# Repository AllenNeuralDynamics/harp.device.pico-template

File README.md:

# harp.device.pico-template

An RP2040-based Harp hardware/firmware project template.

## Features
* predefined *.gitignore* file to remove extraneous KiCAD (hardware) files.
### Hardware
* Schematic template for a generic Harp Device including:
  * ground-isolated Full Speed USB communication
  * 3.5mm audio jack for Harp-protocol time synchronization
  * RP2040 MCU and required "jellybean" components including:
    * 2MB external flash (Winbond MPN: W25Q16JVUXIQ TR).
  * 2 power supply chain options for power derived from either USB directly or from a DC barrel jack.
* Basic PCBA Layout with size hints for various existing enclosures
  * DC Barrel Jack (2.1 x 5.5mm, positive center)
  * USBC
  * 3.5mm audio jack for Harp synchronization signal
  * Ground lug
### Firmware
* basic "hello-world" project with corresponding file structure
* populated CMakeLists.txt for compliation
* placeholder USB descriptors for Manufacturer and Description fields (in the CMakeLists.txt)
* compilation [instructions](./firmware/README.md)
* harp protocol core library included as a submodule [harp.core.rp2040](https://github.com/AllenNeuralDynamics/harp.core.rp2040)

# Using this template
Start by clicking the "Use this Template" button in the upper right corner, or click [here](https://github.com/new?template_name=harp.device.pico-template&template_owner=AllenNeuralDynamics).
## Repository Setup
* If the project has a corresponding Allen Institute SIPE project number, prepend the repository description with: `{SIPE Project Number}:`.
* add the tag `Harp`
* Long-term: remove these instructions!

## Hardware
* Remove all unused hardware folder starter projects.
* 🔧 Design your hardware.
* In the PCBA silkscreen, add:
  * SIPE part number with full hardware semantic version appended in the format: `{SIPE Project Number}-E-{hw major}-{hw minor}-{hw patch}`. Version number fields range from 1-999 and include leading zeros.
  * [QR code](https://www.the-qrcode-generator.com/) linking to the Github repository.

## Firmware
* Update the *Manufacturer* and *Description* USB descriptors in the CMakeLists.txt
* 📝 Write your firmware.

# Github Release Conventions
Releases specify any vetted changes to the hardware or firmware.

Each release specifies:
* semantic versions of changed elements: hardware or firmware.
* SIPE part number (or part numbers if multiple are compatible)

Each hardware release includes:
* STEP file of the PCB named with the SIPE part number
* schematic (PDF)
* Gerber files (with logos removed) of the PCBA
* Position files for component placement
* Bill-of-Materials for the PCBA

Each hardware release specifies:
* compatible SIPE part number(s)

> [!NOTE]
> SIPE part numbers only encode hardware semantic version major number, so multiple minor/patch hardware releases may point to the same SIPE part number.

> [!NOTE]
> It is possible for a project to have PCBA variants--possibly with very different functionality. In this case, reserve a hardware major version range (>100 suggested) for this variant and treat it as a distinct hardware release (i.e: with all corresponding included hardware files).

Each firmware release specifies:
* firmware semantic version
* compatible hardware (SIPE part number or part number range).

Each firmware release includes:
* compiled binary file (**\*.uf2**) of the firmware.

## Release Title
The release title is specified as follows:

`hw{hw major}.{hw minor}.{hw patch}-fw{fw major}.{fw minor}.{fw patch}`

If the release has firmware-only changes, you can drop the `hw*` section, and vice versa.

> [!NOTE]
> After Oct 2024, hardware major fields on all future releases will be equivalent to the major version number of the SIPE part number. See the [SIPE PCBA part numbering standard](https://alleninstitute.sharepoint.com/:w:/s/Instrumentation/EYsRN8q4jHJDmG5DNf-gaM0Bq418YMXollFxtB9d_NZ6pg?e=joLAvU) for more details.

The above field spec enables automation utilities to find the latest firmware version and automatically update compatible hardware. Since releases can include changes to some, but not other fields, unchanged fields are omitted. (i.e: firmware-only changes would be titled `fw{fw major}.{fw minor}.{fw patch}`.)

## Creating a New Release
1. Make a [git tag](https://git-scm.com/book/en/v2/Git-Basics-Tagging) based on the commit in the main branch that you'd like to create the release from. Use the naming convention specified in the [Release Title](#release-title) section.
2. Push the tag to Github.
3. From the repository's corresponding *Release* page, create a new release from the tag you just added. Give it the same title as the tag.
4. If the release includes new _firmware_, compile it locally, and upload a copy of the *.uf2* file as an attachment.
5. If the release includes new _hardware_, upload: (1) the gerber files (zipped), (2) the position files, (3) any manufacturing notes, (4) the bill-of-materials, (5) a PDF of the schematic.

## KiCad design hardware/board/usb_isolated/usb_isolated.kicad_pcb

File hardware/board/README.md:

## Overview

These schematic and layout designs have been vetted on prior devices.

High Level Specs:
    * USBC connector (ESD protected with TVS diode).
    * Audio jack connector for Harp synchronization signal (ESD protected with TVS diode).

Component Specs:
    * aqueous washable
    * commonly available components (no end-of-life or last-time-buy)

Layout Specs:
    * 4-layer PCB
        * signal (top), ground, power, signal (bottom)
    * 6-mil traces, 6-mil spacing (0.1524mm)
    * no microvias
    * smallest resistor/capacitor sizes are 0402.
    * Footprints default to "non-hand-soldering"-style.

MCU Schematic Specs:
    * 12MHz oscillator, +/-2.5ppm
    * 16MB flash, Winbond W25Q16JVUXIQ

### USB-Isolated-Only Template Specs
    * Electrically isolated from PC, Analog Devices ADUM4160

## Instructions

Pick a template folder (or none!) as a starting point and delete the remaining other folders.

Rename the folder and all subfolder files of the same name to the name of your project.

Delete the instructions in this file.

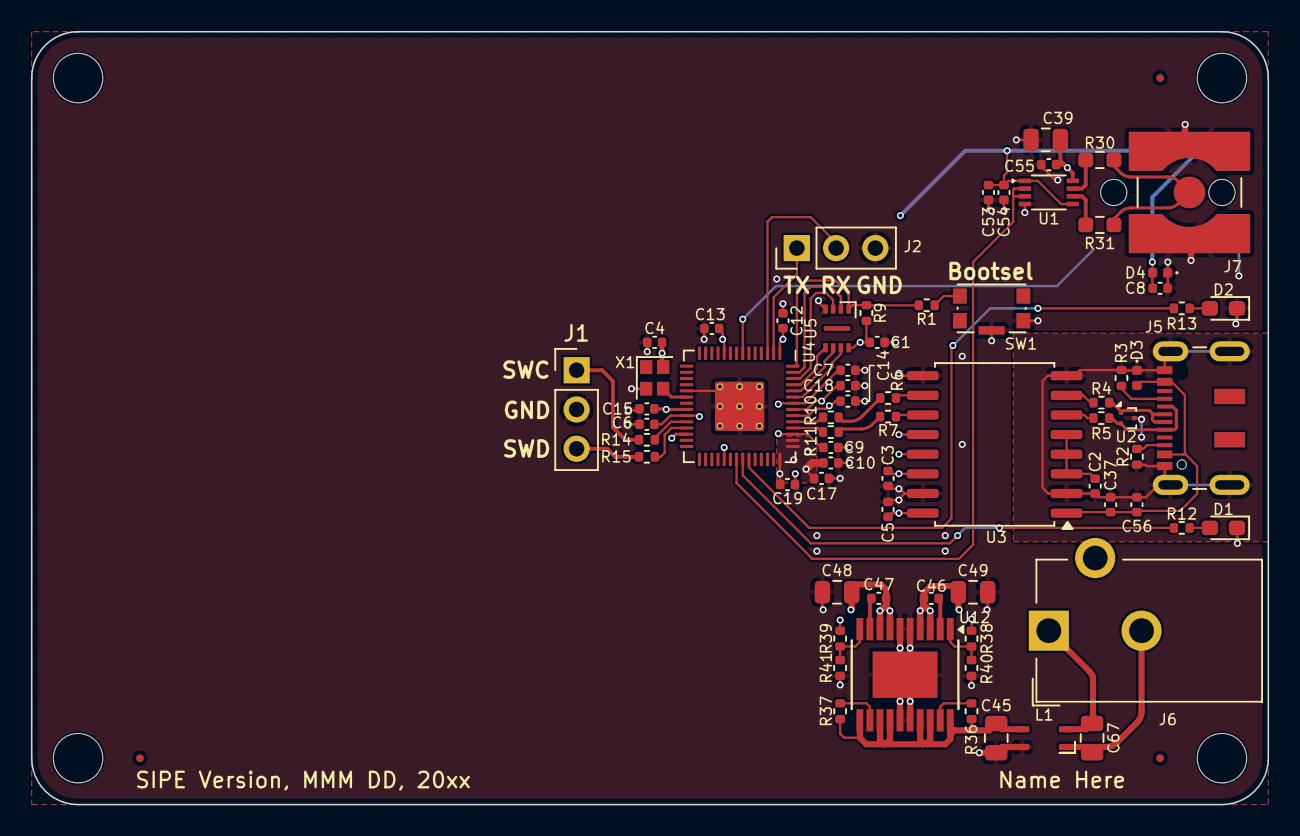
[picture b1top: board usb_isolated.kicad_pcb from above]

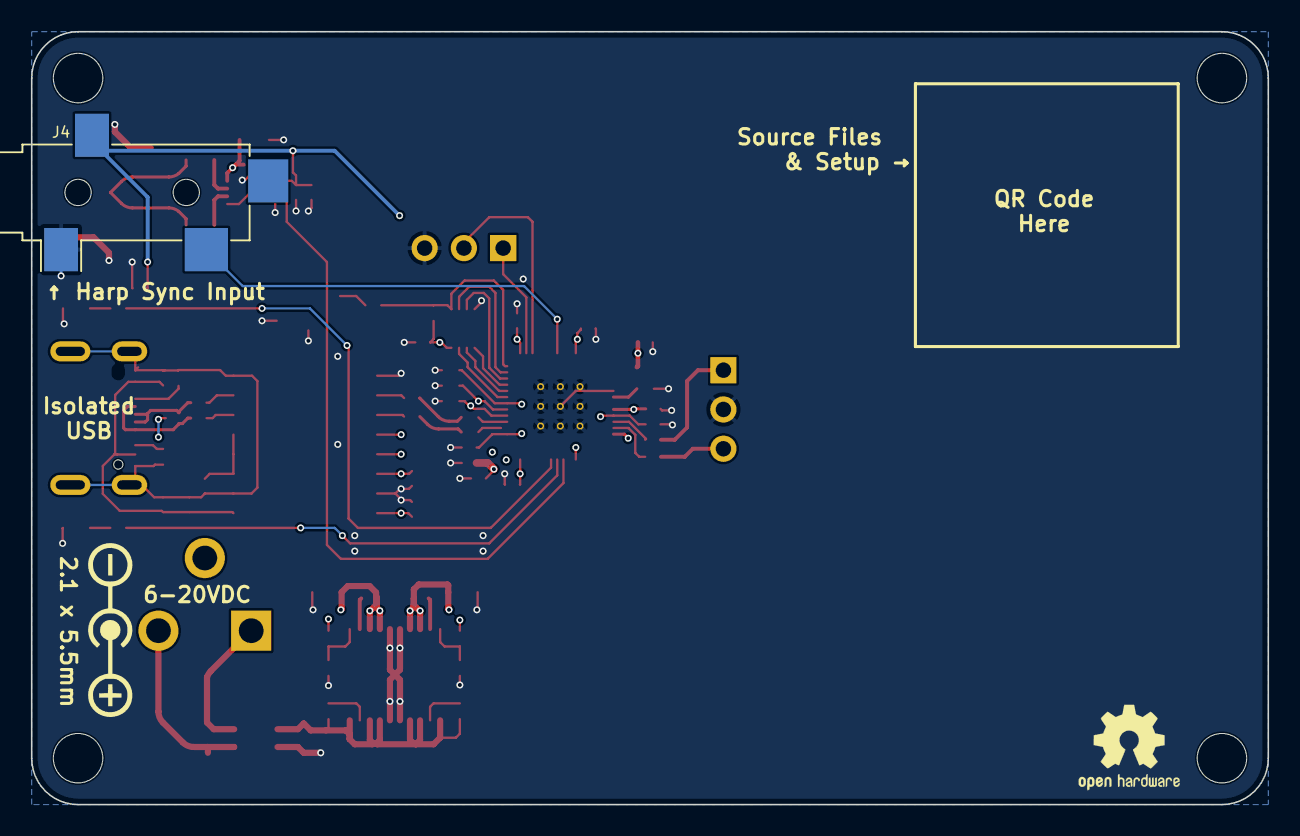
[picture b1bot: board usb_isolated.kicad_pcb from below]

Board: 4 copper layers, 80.0 x 50.0 mm, 75 parts (3 on the bottom side), 51 nets.

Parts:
C1, C2, C3, C5, C6, C7, C12, C13, C14, C15, C17, C18, C19, C37, C54, C55: 100nF; C_0402_1005Metric
C4, C46, C47: 10nF; C_0402_1005Metric
C8, C9, C10, C53, C56: 1uF; C_0402_1005Metric
C39, C48: 10uF; C_0805_2012Metric
C45, C67: 3.3uF; C_0805_2012Metric
C49: 22uF; C_0805_2012Metric
D1, D2: LED; LED_0603_1608Metric_Pad1.05x0.95mm_HandSolder
D3, D4: D_TVS; D_0402_1005Metric
FID1, FID2, FID3: Fiducial; Fiducial_0.5mm_Mask1mm
G3: LOGO
J1, J2: Conn_01x03_Male; PinHeader_1x03_P2.54mm_Vertical
J4: AudioJack3; Jack_3.5mm_CUI_SJ-3524-SMT_Horizontal
J5: USB_C_Receptacle_USB2.0; USB_C_Receptacle_JAE_DX07S016JA1R1500
J6: Barrel_Jack_Switch; BarrelJack_CUI_PJ-102AH_Horizontal
J7: Conn_Coaxial; SMA_TE_Connectivity_CONSMA002-SMD-G-T_Horizontal
L1: L_Coupled_1423; L_CommonModeChoke_TDKCorporation_1210
R1: 1K; R_0402_1005Metric
R2, R3: 5K1; R_0402_1005Metric
R4, R5, R6, R7: 24; R_0402_1005Metric
R9: 10K; R_0402_1005Metric
R10, R11: 27; R_0402_1005Metric
R12, R13: 680; R_0402_1005Metric
R14, R15: 100; R_0402_1005Metric
R30, R31: 100; R_0603_1608Metric_Pad0.98x0.95mm_HandSolder
R36, R37: 1M; R_0402_1005Metric
R38: 309K; R_0402_1005Metric
R39: 172K; R_0402_1005Metric
R40, R41: 100K; R_0402_1005Metric
REF1: OSHW-Logo2_7.3x6mm_SilkScreen
SW1: SW_Push_1P1T-SH_NO_Vertical_Wuerth_WS-TASV
U1: 74LVCH2T45DC; VSSOP-8_2.3x2mm_P0.5mm
U2: TPD2EUSB30; Texas_DRT-3
U3: ADUM4160; SOIC-16W_7.5x10.3mm_P1.27mm
U4: RP2040; RP2040-QFN-56
U5: W25Q16JVUXIQ; Winbond-8USON-2x3mm
U12: LT3030; ETSSOP-20-1EP_4.4x6.5mm_P0.65mm_EP3x4.2mm
X1: ECS-TXO-2016; Crystal_SMD_2016-4Pin_2.0x1.6mm

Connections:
+1V1: C6.2, C7.2, C9.1, U4.23 (DVDD), U4.45 (VREG_VOUT), U4.50 (DVDD)
+3.3V: C1.2, C3.2, C4.2, C5.2, C8.1, C10.1, C12.2, C13.2, C14.2, C15.2, C17.2, C18.2, C19.2, C47.1, C48.1, C53.1, C54.2, D4.2 (A2), J4.R, R9.2, R39.1, U1.1 (VCCA), U1.5 (DIR), U3.12 (PIN), U3.13 (SPD), U3.14 (VDD2), U3.16 (VBUS2), U4.1 (IOVDD), U4.10 (IOVDD), U4.22 (IOVDD), U4.26 (RUN), U4.33 (IOVDD), U4.42 (IOVDD), U4.43 (ADC_AVDD), U4.44 (VREG_IN), U4.48 (USB_VDD), U4.49 (IOVDD), U5.8 (VCC), U12.7 (OUT2), U12.8 (OUT2), X1.4 (VDD)
+5V: C39.1, C46.1, C49.1, C55.2, R38.1, U1.8 (VCCB), U12.3 (OUT1), U12.4 (OUT1)
+12V: C67.1, J6.1, L1.2
/Harp Core RP2040 + Isolated USB/D+: J5.A6 (D+), J5.B6 (D+), R4.1, U2.1 (D+)
/Harp Core RP2040 + Isolated USB/D-: J5.A7 (D-), J5.B7 (D-), R5.1, U2.2 (D-)
/Harp Core RP2040 + Isolated USB/DD+: R6.2, R10.2
/Harp Core RP2040 + Isolated USB/DD-: R7.2, R11.2
/Harp Core RP2040 + Isolated USB/HARP_CLK_SYNC: J4.T, U4.7 (GPIO5)
/Harp Core RP2040 + Isolated USB/QSPI_CLK: U4.52 (QSPI_SCLK), U5.6 (CLK)
/Harp Core RP2040 + Isolated USB/QSPI_CS: R1.2, R9.1, U4.56 (QSPI_SS), U5.1 (~CS)
/Harp Core RP2040 + Isolated USB/QSPI_D0: U4.53 (QSPI_SD0), U5.5 (DI(IO0))
/Harp Core RP2040 + Isolated USB/QSPI_D1: U4.55 (QSPI_SD1), U5.2 (DO(IO1))
/Harp Core RP2040 + Isolated USB/QSPI_D2: U4.54 (QSPI_SD2), U5.3 (IO2)
/Harp Core RP2040 + Isolated USB/QSPI_D3: U4.51 (QSPI_SD3), U5.7 (IO3)
/Harp Core RP2040 + Isolated USB/SWCLK: J1.1, R14.1
/Harp Core RP2040 + Isolated USB/SWDIO: J1.3, R15.1
/Harp Core RP2040 + Isolated USB/TTL_OUT: U1.2 (1A), U1.3 (2A), U4.35 (GPIO23)
/Harp Core RP2040 + Isolated USB/UART0_RXD: J2.2, U4.3 (GPIO1)
/Harp Core RP2040 + Isolated USB/UART0_TXD: J2.1, U4.2 (GPIO0)
/Harp Core RP2040 + Isolated USB/USB_Boot: R1.1, SW1.2
/Harp Core RP2040 + Isolated USB/VDD1: C2.2, U3.3 (VDD1), U3.4 (PDEN), U3.5 (SPU)
GND: C1.1, C3.1, C4.1, C5.1, C6.1, C7.1, C8.2, C9.2, C10.2, C12.1, C13.1, C14.1, C15.1, C17.1, C18.1, C19.1, C39.2, C45.2, C48.2, C49.2, C53.2, C54.1, C55.1, D1.1 (K), D2.1 (K), D4.1 (A1), J1.2, J2.3, J4.S, J7.2 (Ext), L1.4, R40.1, R41.1, SW1.4, SW1.SH, U1.4 (GND), U3.9 (GND2), U3.15 (GND2), U4.19 (TESTEN), U4.57 (GND), U5.4 (GND), U12.5 (GND), U12.6 (GND), U12.15 (GND), U12.16 (GND), U12.21 (GND), X1.2 (GND)
GND1: C2.1, C37.1, C56.2, D3.1 (A1), J5.A1 (GND), J5.A12 (GND), J5.B1 (GND), J5.B12 (GND), J5.S1 (SHIELD), R2.2, R3.2, U2.3 (GND), U3.2 (GND1), U3.8 (GND1)
GND2: C67.2, J6.2, L1.1
IN1: C45.1, L1.3, R36.1, R37.1, U12.11 (~SHDN2), U12.13 (IN2), U12.14 (IN2), U12.17 (IN1), U12.18 (IN1), U12.20 (~SHDN1)
unnamed: D1.2 (A), R12.2
unnamed: D2.2 (A), R13.2
unnamed: J5.A5 (CC1), R2.1
unnamed: J5.B5 (CC2), R3.1
unnamed: J7.1 (In), R30.2, R31.2
unnamed: R30.1, U1.7 (1B)
unnamed: R31.1, U1.6 (2B)
unnamed: R6.1, U3.10 (DD+)
unnamed: R7.1, U3.11 (DD-)
unnamed: R4.2, U3.7 (UD+)
unnamed: R5.2, U3.6 (UD-)
unnamed: R12.1, U4.36 (GPIO24)
unnamed: R13.1, U4.37 (GPIO25)
unnamed: R14.2, U4.24 (SWCLK)
unnamed: R15.2, U4.25 (SWD)
unnamed: R11.1, U4.46 (USB_DM)
unnamed: R10.1, U4.47 (USB_DP)
unnamed: U4.20 (XIN), X1.3 (OUT)
unnamed: R38.2, R40.2, U12.1 (ADJ1)
unnamed: R39.2, R41.2, U12.10 (ADJ2)
unnamed: C46.2, U12.2 (BYP1)
unnamed: C47.2, U12.9 (BYP2)
unnamed: R36.2, U12.19 (PWRGD1)
unnamed: R37.2, U12.12 (PWRGD2)
VBUS: C37.2, C56.1, D3.2 (A2), J5.A4 (VBUS), J5.A9 (VBUS), J5.B4 (VBUS), J5.B9 (VBUS), U3.1 (VBUS1)

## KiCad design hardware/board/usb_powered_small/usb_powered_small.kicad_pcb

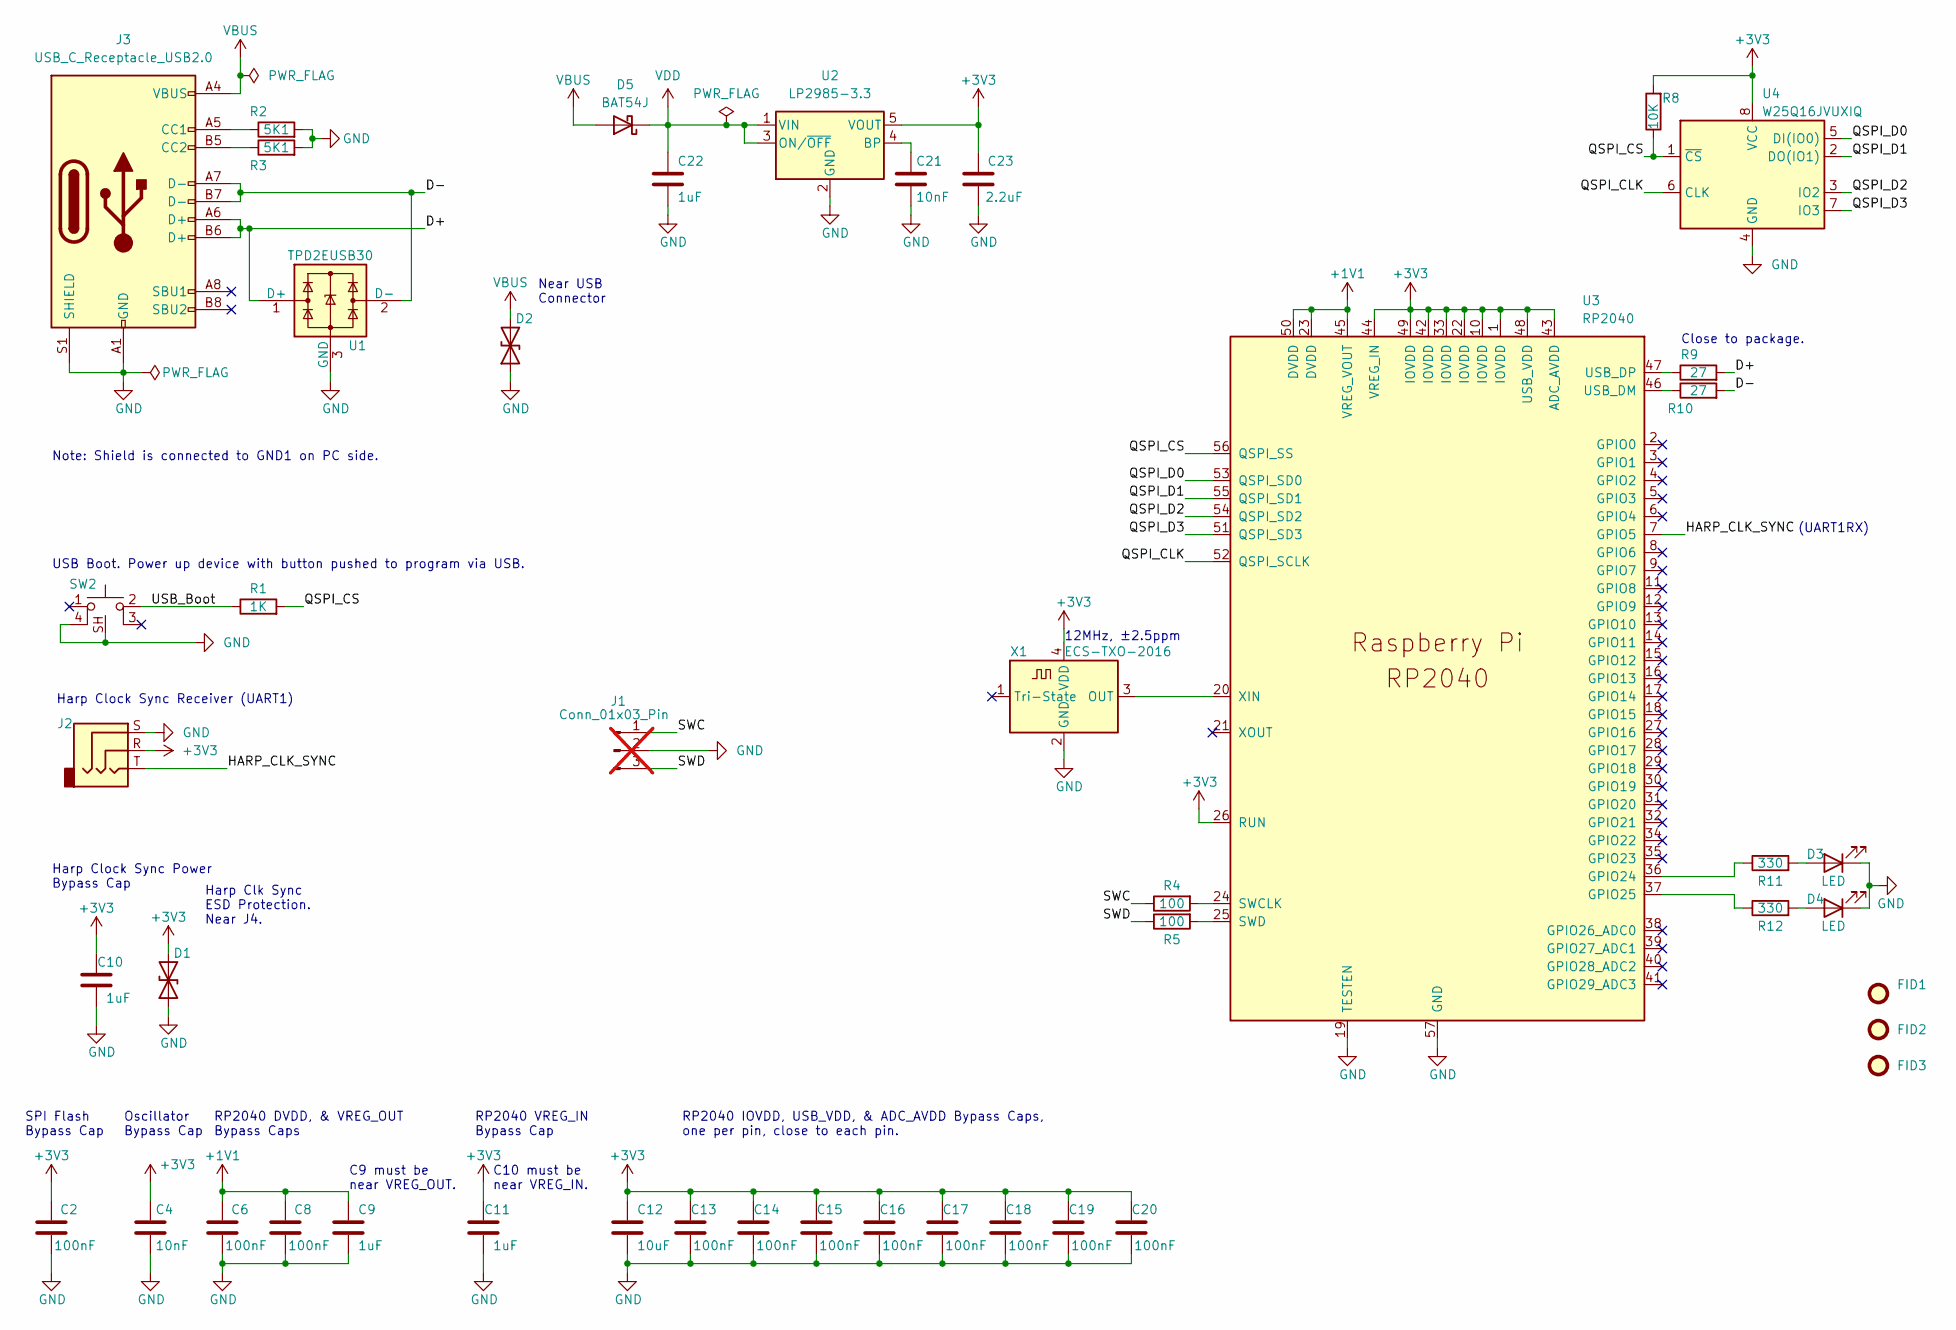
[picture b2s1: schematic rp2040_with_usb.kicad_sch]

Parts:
C2, C6, C8, C13, C14, C15, C16, C17, C18, C19, C20: 100nF; C_0402_1005Metric; Rated Voltage 16V; Tolerance 10%
C4, C21: 10nF; C_0402_1005Metric; Rated Voltage 25V; Tolerance 2%
C9, C10, C11, C22: 1uF; C_0402_1005Metric; Rated Voltage 35V
C12: 10uF; C_0805_2012Metric; Rated Voltage 25V
C23: 2.2uF; C_0402_1005Metric; Rated Voltage 10V
D1, D2: D_TVS; D_0402_1005Metric
D3, D4: LED; LED_0603_1608Metric_Pad1.05x0.95mm_HandSolder
D5: BAT54J; D_SOD-323F
FID1, FID2, FID3: Fiducial; Fiducial_0.5mm_Mask1mm
J1: Conn_01x03_Pin; PinHeader_1x03_P2.54mm_Vertical; not fitted
J2: AudioJack3; Jack_3.5mm_CUI_SJ-3523-SMT_Horizontal
J3: USB_C_Receptacle_USB2.0; USB_C_Receptacle_JAE_DX07S016JA1R1500
R1: 1K; R_0402_1005Metric; Tolerance 1%
R2, R3: 5K1; R_0402_1005Metric; Tolerance 1%
R4, R5: 100; R_0402_1005Metric
R8: 10K; R_0402_1005Metric; Tolerance 1%
R9, R10: 27; R_0402_1005Metric; Tolerance 1%
R11, R12: 330; R_0402_1005Metric; Tolerance 0.1%
SW2: SW_Push_1P1T-SH_NO_Vertical_Wuerth_WS-TASV
U1: TPD2EUSB30; Texas_DRT-3
U2: LP2985-3.3; SOT-23-5
U3: RP2040; RP2040-QFN-56
U4: W25Q16JVUXIQ; Winbond-8USON-2x3mm
X1: ECS-TXO-2016; Crystal_SMD_2016-4Pin_2.0x1.6mm; Tolerance ±2.5ppm

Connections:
+1V1: C6.2, C8.2, C9.1, U3.23 (DVDD), U3.45 (VREG_VOUT), U3.50 (DVDD)
+3V3: C2.2, C4.1, C10.1, C11.1, C12.1, C13.2, C14.2, C15.2, C16.2, C17.2, C18.2, C19.2, C20.2, C23.2, D1.2 (A2), J2.R, R8.2, U2.5 (VOUT), U3.1 (IOVDD), U3.10 (IOVDD), U3.22 (IOVDD), U3.26 (RUN), U3.33 (IOVDD), U3.42 (IOVDD), U3.43 (ADC_AVDD), U3.44 (VREG_IN), U3.48 (USB_VDD), U3.49 (IOVDD), U4.8 (VCC), X1.4 (VDD)
/Harp Core RP2040 + USB/D+: J3.A6 (D+), J3.B6 (D+), R9.2, U1.1 (D+)
/Harp Core RP2040 + USB/D-: J3.A7 (D-), J3.B7 (D-), R10.2, U1.2 (D-)
/Harp Core RP2040 + USB/HARP_CLK_SYNC: J2.T, U3.7 (GPIO5)
/Harp Core RP2040 + USB/QSPI_CLK: U3.52 (QSPI_SCLK), U4.6 (CLK)
/Harp Core RP2040 + USB/QSPI_CS: R1.2, R8.1, U3.56 (QSPI_SS), U4.1 (~CS)
/Harp Core RP2040 + USB/QSPI_D0: U3.53 (QSPI_SD0), U4.5 (DI(IO0))
/Harp Core RP2040 + USB/QSPI_D1: U3.55 (QSPI_SD1), U4.2 (DO(IO1))
/Harp Core RP2040 + USB/QSPI_D2: U3.54 (QSPI_SD2), U4.3 (IO2)
/Harp Core RP2040 + USB/QSPI_D3: U3.51 (QSPI_SD3), U4.7 (IO3)
/Harp Core RP2040 + USB/SWC: J1.1, R4.1
/Harp Core RP2040 + USB/SWD: J1.3, R5.1
/Harp Core RP2040 + USB/USB_Boot: R1.1, SW2.2
GND: C2.1, C4.2, C6.1, C8.1, C9.2, C10.2, C11.2, C12.2, C13.1, C14.1, C15.1, C16.1, C17.1, C18.1, C19.1, C20.1, C21.2, C22.2, C23.1, D1.1 (A1), D2.1 (A1), D3.1 (K), D4.1 (K), J1.2, J2.S, J3.A1 (GND), J3.A12 (GND), J3.B1 (GND), J3.B12 (GND), J3.S1 (SHIELD), R2.2, R3.2, SW2.4, SW2.SH, U1.3 (GND), U2.2 (GND), U3.19 (TESTEN), U3.57 (GND), U4.4 (GND), X1.2 (GND)
unnamed: D3.2 (A), R11.2
unnamed: D4.2 (A), R12.2
unnamed: J3.A5 (CC1), R2.1
unnamed: J3.B5 (CC2), R3.1
unnamed: C21.1, U2.4 (BP)
unnamed: R11.1, U3.36 (GPIO24)
unnamed: R12.1, U3.37 (GPIO25)
unnamed: R4.2, U3.24 (SWCLK)
unnamed: R5.2, U3.25 (SWD)
unnamed: R10.1, U3.46 (USB_DM)
unnamed: R9.1, U3.47 (USB_DP)
unnamed: U3.20 (XIN), X1.3 (OUT)
VBUS: D2.2 (A2), D5.2 (A), J3.A4 (VBUS), J3.A9 (VBUS), J3.B4 (VBUS), J3.B9 (VBUS)
VDD: C22.1, D5.1 (K), U2.1 (VIN), U2.3 (ON/~OFF)

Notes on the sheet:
C10 must be near VREG_IN.
C9 must be near VREG_OUT.
SPI Flash Bypass Cap
Close to package.
Harp Clock Sync Power Bypass Cap
Harp Clock Sync Receiver (UART1)
Oscillator Bypass Cap
RP2040 DVDD, & VREG_OUT Bypass Caps
RP2040 VREG_IN Bypass Cap
USB Boot. Power up device with button pushed to program via USB.
(UART1RX)
RP2040 IOVDD, USB_VDD, & ADC_AVDD Bypass Caps, one per pin, close to each pin.
Near USB Connector
Note: Shield is connected to GND1 on PC side.
12MHz, ±2.5ppm
Harp Clk Sync ESD Protection. Near J4.

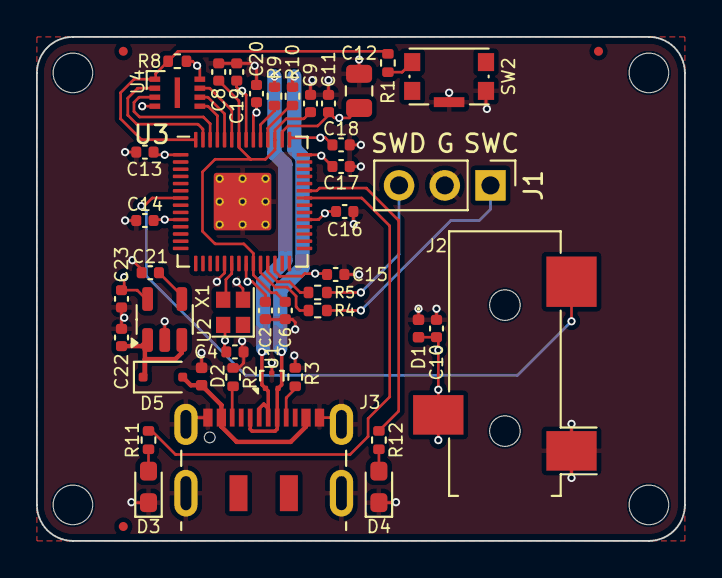
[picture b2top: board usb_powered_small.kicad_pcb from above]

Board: 4 copper layers, 36.0 x 28.0 mm, 46 parts (0 on the bottom side), 29 nets.

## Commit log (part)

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2023-12-11 add rp2040 harp core submodule
2023-12-12 add compilation readme; update CMakeLists.txt
2024-05-20 add pcb starting points
2024-06-21 bugfix CMakeLists.txt
2024-07-24 append git has to executable name
2024-11-14 Update README.md
    draft release convention
2025-02-19 update how pico sdk path is searched for
2025-02-21 cleanup template config, add git hash, update pico core
2025-03-07 update compilation instructions
2025-03-07 fix variable definition from environment variable
2025-03-07 Update README.md
    draft windows toolchain setup.
2025-03-10 update usb isolated pcba layout
2025-04-29 update remote url for pico core
